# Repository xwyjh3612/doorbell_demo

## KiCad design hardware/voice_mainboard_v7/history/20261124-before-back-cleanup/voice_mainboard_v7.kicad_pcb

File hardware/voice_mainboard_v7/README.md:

# 语音对讲主板V7工作版

## 当前RGB版本

2026-11-24：单颗WS2812B-2020-V6（C52917434）已加入主板正面上沿，位置(72mm, 3mm)。GPIO39对应ESP模组32脚，经330Ω电阻驱动DI；100nF作局部去耦。厂家标明支持3.3V供电，新板的供电容差、启动、低压及光学效果仍需实测。

| 指示 | 含义 |
|---|---|
| 红色慢闪 | 未联网 / MQTT未就绪 |
| 绿色双闪 | 在线待机 |
| 蓝色快闪 | 呼叫、呼入、连接中 |
| 蓝色长亮带短熄灭 | 通话中 |

灯读取本地状态，由低优先级任务和RMT硬件驱动，不发送额外AT命令，不改变音频队列、主动丢旧包或官方协议。它不是独立供电指示灯或硬件看门狗。配置`CONFIG_VOICE_STATUS_INDICATOR_ENABLE`默认关闭；`tools/build-firmware.ps1 -Variant mainboard-v7`开启电源监测及RGB，开发板`voice-radar60`不包含这两项。两种固件的配置、编译包含/排除与链接符号已验证，灯色/闪烁/长运行时间的主机逻辑测试通过，未刷机或测试新主板。

本次按官方表核对全部已用GPIO，修复原版实际接到GPIO41的充电控制：GPIO38应接模组31脚，模组34脚实际为GPIO41。新RGB原理图、PCB、符号库与固件一致。旧版GPIO38暂停充电的说明不适用于未纠正的旧PCB。

当前ERC/DRC错误及警告、未连接、原理图连接差异均为0，实际填充GND为一个连通分量。只证明CAD连接，不是完整电气仿真或生产放行。当前证据以[rgb-validation.json](exports/rgb-validation.json)及[新版预览](exports/review.html)为准；加灯前的文件与检查在[历史快照](history/20261124-before-rgb/voice_mainboard_v7.kicad_pcb)。下文局部整理数据和费用均属于加灯前版本。

[公开价格](https://item.szlcsc.com/55827425.html)：少量0.5585元/颗、100颗0.3469元、1000颗0.3198元。加电阻、电容后按约0.4元/台材料预算；电阻、电容并未全部取得本次新报价，新增贴装/换料费用仍需审单。当前默认装配由116增加到119个元件。此前51.46/52.33元的条件预算需另加RGB材料和新增加工费，不能当成新版整单报价。

2026-11-24，用户授权由设计方决定技术路线。采用100×75mm、两层板，保留现有功能，按可靠性、成本和可制造性重新整理布局。

**加灯前完成的是局部供电布局优化与背面长地线清理，整板重新布局、器件定型和实物验证尚未完成，未生产放行。** V6原板保留；V7采用V6已通过几何检查的走线优化候选作为起点，不改变固件协议与主动丢旧包策略。

## 当前技术决定

| 项目 | 决定 | 状态 |
|---|---|---|
| 板层及尺寸 | 100×75mm两层，先保留现有接口和安装孔 | 已落实 |
| 主控 | 保留ESP32-S3-WROOM-1-N8R8，不为了减少几元改为需另外设计Flash/PSRAM的裸芯片方案 | 沿用；仍需采购报价及模组配置核对 |
| 4G | 按ML307C-DL贴装规划，第一阶段沿用AT通信；USB作为硬件备用，需重新布局与独立验证 | 主方案明确；新模组实测及USB验证未完成 |
| 音频 | 保留当前I2S功放及INMP441模块接口；先改善供电去耦和回流，不改已测试的音频协议 | 局部去耦已调整；音频整体分区待重排 |
| 电源 | 5V/2A外电，正常时直供系统；单节4.2V锂离子电池备用，经保护、升压和切换接管 | 架构明确；具体电芯、NTC、低电量峰值与热测试仍待确定 |
| 卡座 | 优先国产翻盖Nano SIM、保留检测功能；SMN-305-ARP7（C720512）为优先核查对象 | 公开1000件阶梯参考0.5977元。图纸下载返回403、未获得对应封装证据，因此暂未换入；现板仍保留JAE卡座 |
| 走线 | 水平/垂直优先、必要处45°；去掉绕路和无意义折返；电源、USB、射频按各自电气要求处理 | 部分落实；整板分区重排未完成 |
| 充电温度 | 目标电芯需明确允许充电温度；不沿用V6约−7℃的低温门限。优先设计带容差裕量的保守窗口 | 电芯与NTC准确规格确定后重算；现工作版阻值尚未更改 |
| 电量 | ESP ADC估算电量；保留外电接入和实际电源选择检测 | 现有硬件/代码接口保留；新板验收未完成 |

## 本次完成的局部修改

- 功放100nF C62与U14电源焊盘中心直线距离，从约5.63mm降到约1.95mm。
- 功放10µF C61与对应电源焊盘距离约4.21mm，较原位置缩短；它不是当前最佳完整布局，整板重排时还要继续改善。
- 充电输入C67与U16电源焊盘距离，从约8.05mm降到约2.62mm。
- 充电电池侧C68与U16 BAT焊盘距离，从约5.34mm降到约3.75mm。
- 重接局部电源与地，清理因电容移位遗留的无效支路。供电路径连通不代表动态、热与最大电流已经验证。
- 保留前一候选对主输入细线的修复。

上述数字是焊盘中心直线距离，不是环路长度、等效电感或实测噪声结果。[加灯前局部检查记录](history/20261124-before-rgb/exports/local-layout-validation.json)绑定当时PCB哈希；不使用旧版检查为新版背书。

## 后续工程工作

按电源局部环路→主控/音频分区→4G/SIM/天线区→USB接口与差分线路→整板规则、制造BOM和成本的顺序推进。所有局部修改都重新运行原生DRC和原理图连接一致性检查。

生产前仍须完成准确料号/封装、NTC温度窗口、实际电芯、低电量启动与接管、峰值电流及温升、USB/RF资格、刷机与长通话验证。软件模型和ERC/DRC均不代替新主板实测。

## 背面整理结果与量产核算

2026-11-24新增：保留焊盘位置、原理图连接、电池隔离负极及局部电源回流，简化可安全缩短的连续走线；清理与铺铜重复的长地线。两处失去接地的焊盘（C10、Q7）补接背面地铜，新增两个地过孔，保留原有地过孔。

| 背面指标 | 整理前 | 整理后 |
|---|---:|---:|
| 线段数 | 1109 | 571 |
| 非共线二路连接点（连续转角） | 632 | 309 |
| 地线线段数 | 664 | 148 |

上述数字统计铜线对象；移除冗余地线后由实际铺铜承担连接，不能将铜线长度下降解读为回流路径缩短或电阻降低。原生DRC错误/警告/未连接/原理图连接差异均为0，包含孔洞的填充地铜、焊盘、线与通孔连通审查为一个GND分量。该审查只证明连接，未验证电源动态、温升或EMC。

整理前PCB及其哈希记录保存在[历史快照](history/20261124-before-back-cleanup/voice_mainboard_v7.kicad_pcb)。加灯前结果见[背面前后对比](history/20261124-before-rgb/exports/review.html)与[当时审查记录](history/20261124-before-rgb/exports/back-cleanup-validation.json)。走线视图暂隐藏铺铜，实际生产工作文件保留铺铜。

1000块的降本核算：按用户4G 10元、ESP32-S3 N8R8 12元目标价，其余有公开/历史候选参考的优先重算，功放采用4.52元公开参考价。国产SIM C720512图纸、封装及检测触点尚待核，未写入PCB。全接口候选方案约52.33元/块；仅雷达与TTL排针不默认安装、保留焊孔的可选量产方案约51.46元/块。后者插件节省按历史0.09元/焊点推算，本次网站防护页面阻止取得新公开计算结果，仍非嘉立创完整审单报价。按已保存公开4G/ESP参考价替代用户目标，可选量产方案将增加15.01元/块。

成本与装配选项尚未改变当前样机的默认BOM；加灯前样机保留116个装配元件，当前RGB工作版为119个。详见[逐项成本与采购边界](cost/量产降本核算.md)。本次不因走线整理计入PCB单价节省。

## 充电与无电池使用状态

2026-11-24核查：当前未实现80%停充/70%再充；现有电源监测仅在呼叫、通话、OTA暂停充电，功能默认关闭。TP4056-MS按约4.2V、名义300mA充电。已有GPIO38→Q7→CE可供后续实现电量迟滞控制，无需另加控制芯片。

外电通路独立于电池，设计上支持不装电池、仅插5V电源。电池及NTC均不接时，现温度分压约0.89×VCC，按芯片规格暂停充电；整板外电启动与负载能力仍待实板测试。ADC读到电压不能单独证明已安装电池，固件不得将无电芯的输出电容电压当作有效SOC。

本次已运行当前阻值的ngspice被动/理想控制子电路，并核对实际PCB引脚网络；未进行电芯化学充放电、充电IC/升降压完整厂家模型或整板电气仿真。现假设10k/B3950 NTC的名义温度窗口约−7～38.5℃，−5℃仍允许充电，必须按选定电芯修正。TEMP短到地会禁用温度监测，不能视为自动停充。详见[充放电与无电池核查记录](exports/charge-supply-audit/充放电核查.md)。

[PCB工作文件](voice_mainboard_v7.kicad_pcb) · [原理图](voice_mainboard_v7.kicad_sch) · [当前检查记录](exports/rgb-validation.json)

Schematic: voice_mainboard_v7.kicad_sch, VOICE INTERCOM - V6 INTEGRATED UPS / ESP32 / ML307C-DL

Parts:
C4, C6, C7, C59, C60: 22u 16V; C_0805_2012Metric
C5: 22u 16V; C_0805_2012Metric; not fitted
C8: OCV471M1ATR-1010 470u 10V; CP_Elec_10x10.5
C10: 10u 10V; C_0805_2012Metric
C11, C13, C14, C15, C16, C17, C18, C58, C62, C69, C70: 100n; C_0603_1608Metric
C12: 33p; C_0603_1608Metric
C19, C29: CL10B103KB8NNNC; C_0603_1608Metric
C20, C28: CL10B104KB8NNNC C1591; C_0603_1608Metric
C24, C25: RF MATCH SHUNT DNP; C_0603_1608Metric; not fitted
C26: 100n MIC; C_0603_1608Metric
C37: 22p MODEM CFF; C_0603_1608Metric
C56: 1u EN delay; C_0603_1608Metric
C57: 22u; C_0805_2012Metric
C61: 10u; C_0805_2012Metric
C63: 22p ESP CFF; C_0603_1608Metric
C64, C65, C66, C71, C72, C73: 22u 10V X5R; C_0805_2012Metric
C67, C68: 10u 10V X5R; C_0805_2012Metric
D1: SRV05-4 MSKSEMI; SOT-23-6
F1: ASMD1812-400-16V C55014590; Fuse_1812_4532Metric
J1: HX DC005-2.5-T 3A C18357600; HX_DC005_2p5_T
J8: MODEM DOWNLOAD STRAP OPEN NORMAL; PinHeader_1x02_P2.54mm_Vertical; not fitted
J10: JAE SF72S006 SIM CANDIDATE; JAE_SIM_Card_SF72S006
J11: LTE ANT U.FL; U.FL_Hirose_U.FL-R-SMT-1_Vertical
J12: MODEM USB SERVICE VBUS DM DP GND; PinHeader_1x04_P2.54mm_Vertical; not fitted
J14: INMP441 MODULE 3V3 GND BCLK WS SD; PinHeader_1x05_P2.54mm_Vertical
J15: SPEAKER BTL + / - NEVER GND; PinHeader_1x02_P2.54mm_Vertical
J16: OPTIONAL RADAR 5V GND RX6 TX8; PinHeader_1x04_P2.54mm_Vertical
J17: EXTERNAL CALL BUTTON; PinHeader_1x02_P2.54mm_Vertical
J18: TTL GND TX43 RX44 5V; PinHeader_1x04_P2.54mm_Vertical
J22: USB HOST RESERVE GND DP20 DM19; PinHeader_1x03_P2.54mm_Vertical; not fitted
J23: 1S CELL + / - / NTC; PinHeader_1x03_P2.54mm_Vertical
L1: SWPA6045S2R2MT C83455; L_Sunlord_SWPA6045S
L4: SWPA6045S2R2MT; L_Sunlord_SWPA6045S
L5: 2.2uH SWPA4030S 3A TARGET; L_Sunlord_SWPA4030S
Q1, Q2, Q4, Q5: 2N7002K-7 C85047; SOT-23
Q3: BSS84,215 C493579; SOT-23
Q6: DMP2035U-7 C110499; SOT-23
Q7: 2N7002K-7; SOT-23
R2: 100k 0.1% MODEM RH; R_0603_1608Metric
R3: 18.7k 0.1% MODEM RL; R_0603_1608Metric
R4, R12, R21, R68, R72, R73, R74: 10k; R_0603_1608Metric
R5, R6, R8, R15, R16, R32, R69: 100k; R_0603_1608Metric
R7: 4.7k AUTO ON DNP; R_0603_1608Metric; not fitted
R9, R10, R11: 22R; R_0603_1608Metric
R13: 0R RF SERIES; R_0603_1608Metric
R14: 10k BOOT; R_0603_1608Metric
R17: 150k 1%; R_0603_1608Metric
R18, R20: 100k 1%; R_0603_1608Metric
R19: 10k 1%; R_0603_1608Metric
R26: 0R USB SERVICE DP; R_0402_1005Metric
R27: 0R USB SERVICE DM; R_0402_1005Metric
R28: 0R USB HOST DP; R_0402_1005Metric; not fitted
R29: 0R USB HOST DM; R_0402_1005Metric; not fitted
R30: 0R VBUS FROM SERVICE; R_0603_1608Metric
R31: 0R VBUS DETECT FROM SYSTEM DNP; R_0603_1608Metric; not fitted
R57: 10k EN; R_0603_1608Metric
R58: 0R RADAR POWER OPTIONAL; R_0603_1608Metric; not fitted
R59: 100k 1% RH ESP; R_0603_1608Metric
R60: 22.1k 1% RL ESP; R_0603_1608Metric
R61: 73.2k 0.1%; R_0603_1608Metric
R62: 10k 0.1%; R_0603_1608Metric
R63: 30k 1% ISET; R_0603_1608Metric
R64: 4k 1% 300mA; R_0603_1608Metric
R65: 6.19k 1% NTC TOP; R_0603_1608Metric
R66: 49.9k 1% NTC BOTTOM; R_0603_1608Metric
R67: 0R NTC LINK; R_0603_1608Metric
R70: 100k 0.1% PR TOP; R_0603_1608Metric
R71: 33.2k 0.1% PR BOTTOM; R_0603_1608Metric
R75: 0R LEFT CHANNEL; R_0603_1608Metric
R76: 0R 12dB; R_0603_1608Metric
SW1, SW2, SW3: TACT 4.5x4.5 SMD; SW_SPST_TL3342
TP1: POWER_BUS; V6_BOARD_TP1
TP2: MODEM_STATE_1V8; V6_BOARD_TP2
TP3: MODEM_NETLIGHT; V6_BOARD_TP3
TP4: DEBUG_ESP_TX43; V6_BOARD_TP4
TP5: DEBUG_ESP_RX44; V6_BOARD_TP5
TP6: GND; V6_BOARD_TP6
TP7: VIN_PROTECTED; V6_BOARD_TP7
TP8: POWER_BUS; V6_BOARD_TP8
TP9: SYS_5V UPS OUTPUT TEST; V6_BOARD_TP9
TP10: ESP_3V3; V6_BOARD_TP10
TP12: MUX ST / GPIO47; V6_BOARD_TP12
TP13: BAT BOOST 5V; V6_BOARD_TP13
TP14: CELL NEG isolated; V6_BOARD_TP14
TP15: DBG_TX_1V8; V6_BOARD_TP15
TP16: DBG_RX_1V8; V6_BOARD_TP16
TP17: MODEM_1V8; V6_BOARD_TP17
U1: ML307C-DL; ML307C_DL_109_LIBRARY_REVIEW
U2, U13: SY8089A1AAC; SOT-23-5
U3, U4, U5: SN74LVC1T45DBVR; SOT-23-6
U7: ESP32-S3-WROOM-1-N8R8; V6_U7_SMD_LAND_MATCH
U14: MAX98357AETE+; V6_U14_SMD_LAND_MATCH
U15: ETA1096E8A; ETA1096_ESOP8
U16: TP4056-MS; SOIC-8-1EP_3.9x4.9mm_P1.27mm_EP2.29x3mm
U17: XB7608AJL; XB7608_CPC5
U18: TPS2117DRLR; TI_DRL0008A
U19: ME2807A30M3G; SOT-23

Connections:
AMP_GAIN: R76.1, U14.2
AMP_SD: R75.2, U14.4
BAT_ADC2: C28.1, R17.2, R18.1, U7.38
BAT_ADC_EN9: Q4.1 (G), R16.1, U7.17
BAT_BOOST_5V: C65.1, C66.1, C73.1, R61.1, TP13.1, U15.7 (OUT), U18.6 (VIN2)
BAT_DIV_SW: Q3.3 (D), R17.1
BAT_GATE: Q3.1 (G), Q4.3 (D), R15.2
BAT_SENSE_IN: C64.1, C68.1, C69.1, C70.1, J23.1, L4.1, Q3.2 (S), R15.1, U15.4 (IN), U16.5 (BAT), U17.1 (VDD), U19.3 (VIN)
BAT_TEMP: R65.2, R66.1, R67.2, U16.1 (TEMP)
BOOST_EN: U15.2 (EN), U19.1 (RESET_N)
BUCK_FB: C37.2, R2.2, R3.1, U2.5 (FB)
BUCK_SW: L1.1, U2.3 (LX)
CALL_BOOT0: J17.1, R14.2, SW1.1, U7.27
CELL_NEG: C69.2, J23.2, TP14.1, U17.2 (CELL_GND), U17.3 (CELL_GND)
CELL_NTC: J23.3, R67.1
CHG_ACTIVE_N: R73.2, U7.25 (IO48), U16.7 (CHRG)
CHG_CE: Q7.3 (D), R68.2, U16.8 (CE)
CHG_DISABLE_IO38: Q7.1 (G), R69.1, U7.34 (IO38)
CHG_FULL_N: R74.2, U7.39 (IO1), U16.6 (STDBY)
CHG_PROG: R64.1, U16.2 (PROG)
DBG_RX_1V8: TP16.1, U1.38 (DBG_RXD)
DBG_TX_1V8: TP15.1, U1.39 (DBG_TXD)
DEBUG_ESP_RX44: J18.3, TP5.1, U7.36
DEBUG_ESP_TX43: J18.2, TP4.1, U7.37
ESP_3V3: C13.1, C15.1, C17.1, C26.1, C57.1, C58.1, C60.1, C63.1, J14.1, L5.2, R4.1, R14.1, R21.1, R57.1, R59.1, R72.1, R73.1, R74.1, TP10.1, U3.1 (VCCA), U3.5 (DIR), U4.1 (VCCA), U5.1 (VCCA), U5.5 (DIR), U7.2 (3V3)
ESP_DTR4: R5.1, U5.3 (A), U7.4
ESP_EN: C56.1, R57.2, SW2.1, U7.3 (EN)
ESP_FB: C63.2, R59.2, R60.1, U13.5 (FB)
ESP_RX18: U4.3 (A), U7.11
ESP_SW: L5.1, U13.3 (SW)
ESP_TX17: R4.2, U3.3 (A), U7.10
ESP_USB_DM19: J22.3, R29.2, U7.13
ESP_USB_DP20: J22.2, R28.2, U7.14
EXT_DETECT_GATE: C29.1, Q5.1 (G), R19.2, R20.1
EXT_PRESENT_N_IO10: Q5.3 (D), R21.2, U7.18
GND: C4.2, C5.2, C6.2, C7.2, C8.2, C10.2, C11.2, C12.2, C13.2, C14.2, C15.2, C16.2, C17.2, C18.2, C19.2, C20.2, C24.2, C25.2, C26.2, C28.2, C29.2, C56.2, C57.2, C58.2, C59.2, C60.2, C61.2, C62.2, C64.2, C65.2, C66.2, C67.2, C68.2, C70.2, C71.2, C72.2, C73.2, D1.2 (GND), J1.2 (SLEEVE_MFR2), J8.2, J10.C5 (GND), J10.CSW (DETECT_COM), J10.SH (SHIELD), J11.2, J12.4, J14.2, J16.2, J17.2, J18.1, J22.1, Q1.2 (S), Q2.2 (S), Q4.2 (S), Q5.2 (S), Q7.2 (S), R3.2, R5.2, R6.2, R7.2, R8.2, R16.2, R18.2, R20.2, R32.2, R60.2, R62.2, R63.2, R64.2, R66.2, R69.2, R71.2, R76.2, SW1.2, SW2.2, SW3.2, TP6.1, U1.1 (GND), U1.10 (GND), U1.27 (GND), U1.34 (GND), U1.36 (GND), U1.37 (GND), U1.40 (GND), U1.41 (GND), U1.45 (GND), U1.46 (GND), U1.47 (GND), U1.48 (GND), U1.70 (GND), U1.71 (GND), U1.72 (GND), U1.73 (GND), U1.88 (GND), U1.89 (GND), U1.90 (GND), U1.91 (GND), U1.92 (GND), U1.93 (GND), U1.94 (GND), U1.95 (GND), U2.2 (GND), U3.2 (GND), U4.2 (GND), U4.5 (DIR), U5.2 (GND), U7.1 (GND), U7.40 (GND), U7.41 (GND), U13.2 (GND), U14.3, U14.11, U14.15, U14.17, U15.1 (GP), U15.8 (GP), U15.9 (AGND_EP), U16.3 (GND), U16.9 (EP), U17.4 (PACK_NEG), U17.5 (PACK_NEG), U18.1 (GND), U19.2 (GND)
I2S_MIC_BCLK14: J14.3, U7.22
I2S_MIC_DATA12: J14.5, U7.20
I2S_MIC_WS13: J14.4, U7.21
I2S_SPK_BCLK15: U7.8, U14.16
I2S_SPK_DATA7: U7.7, U14.1
I2S_SPK_WS16: U7.9, U14.14
MODEM_1V8: C14.1, C16.1, C18.1, R12.1, TP17.1, U1.24 (VDD_EXT), U3.6 (VCCB), U4.6 (VCCB), U5.6 (VCCB)
MODEM_3V8: C6.1, C7.1, C10.1, C11.1, C12.1, C37.1, L1.2, R2.1, TP1.1, TP8.1, U1.42 (VBAT), U1.43 (VBAT)
MODEM_BOOT_N: J8.1, U1.82 (BOOT_MODE)
MODEM_NETLIGHT: TP3.1, U1.16 (NETLIGHT)
MODEM_PWRKEY_N: Q1.3 (D), R7.1, SW3.1, U1.7 (PWR_ON/OFF)
MODEM_RESET_N: C19.1, Q2.3 (D), U1.15 (RESET)
MODEM_STATE_1V8: TP2.1, U1.25 (STATE)
M_DTR_1V8: U1.19 (UART0_DTR), U5.4 (B)
M_RX_1V8: U1.17 (UART0_RXD), U3.4 (B)
M_SIM_CLK: R10.1, U1.13 (USIM0_CLK)
M_SIM_DATA: R9.1, U1.11 (USIM0_DATA)
M_SIM_RESET: R11.1, U1.12 (USIM0_RESET)
M_TX_1V8: U1.18 (UART0_TXD), U4.4 (B)
M_USB_DM: R27.1, R29.1, U1.60 (USB_DM)
M_USB_DP: R26.1, R28.1, U1.59 (USB_DP)
PWRKEY_CTL: Q1.1 (G), R6.1, U7.19
RADAR_5V: J16.1, R58.2
RADAR_RX6: J16.3, U7.6
RADAR_TX8: J16.4, U7.12
RESET_CTL: Q2.1 (G), R8.1, U7.23
REVERSE_GATE: Q6.1 (G), R32.1
RF_ANT: C24.1, R13.1, U1.35 (ANT_MAIN)
RF_FEED: C25.1, J11.1, R13.2
SERVICE_USB_DM: J12.2, R27.2
SERVICE_USB_DP: J12.3, R26.2
SERVICE_USB_VBUS: J12.1, R30.1
SIM_CLK: D1.3 (IO), J10.C3 (CLK), R10.2
SIM_DATA: D1.1 (IO), J10.C7 (IO), R9.2
SIM_DETECT: J10.DSW (DETECT), R12.2, U1.79 (USIM0_DET)
SIM_RESET: D1.4 (IO), J10.C2 (RST), R11.2
SIM_VCC: C20.1, D1.5 (VCC), D1.6 (IO), J10.C1 (VCC), U1.14 (USIM0_PWR)
SPK_MINUS: J15.2, U14.10
SPK_PLUS: J15.1, U14.9
SUPPLY_BAT_N47: R72.2, TP12.1, U7.24 (IO47), U18.8 (ST)
SYS_5V: C4.1, C5.1, C8.1, C59.1, C61.1, C62.1, C72.1, R31.1, R58.1, R75.1, TP9.1, U2.1 (EN), U2.4 (IN), U13.1 (EN), U13.4 (VIN), U14.7, U14.8, U18.2 (VOUT), U18.7 (VOUT_COMMON)
UPS_FB: R61.2, R62.1, U15.5 (FB)
UPS_ISET: R63.1, U15.6 (ISET)
UPS_PR1: R70.2, R71.1, U18.4 (PR1)
UPS_SW: L4.2, U15.3 (SW)
USB_DETECT_5V: R30.2, R31.2, U1.61 (USB_VBUS)
VIN_DC: F1.1, J1.4 (CENTER_PLUS_MFR4), J18.4, R19.1
VIN_FUSED: F1.2, Q6.3 (D)
VIN_PROTECTED: C67.1, C71.1, Q6.2 (S), R65.1, R68.1, R70.1, TP7.1, U16.4 (VCC), U18.3 (VIN1), U18.5 (MODE)

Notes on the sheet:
01 INPUT / MODEM 3.80856V
02 ETA1096 / CHARGE / PROTECT / MUX
03 ML307 / UART / RESET
04 SIM / RF / USB RESERVE
05 ESP / BOOT / ADC / TTL
06 ESP3.315V / I2S AUDIO
07 TEST PADS
V6: V6 UPS: ETA1096 battery boost + TPS2117 external priority; two SY8089A1 bucks; nominal5V audio/radar.
Battery J23 = CELL+ / isolated CELL- / NTC. CELL- must NOT short to systemGND; U17 is protection.
J18 TTL = GND / ESP TX43 / ESP RX44 / adapter5V. Do not parallel TTL5V and main adapter.
SIM JAE footprint retained until exact cheap socket drawing; GPIO6/8 radar; GPIO47 muxST; ADC2 with GPIO9 gate; GPIO38 charge pause; GPIO48/1 charge status.
Electrical/geometry checks do not validate load, startup, temperature, RF, USB or call function.

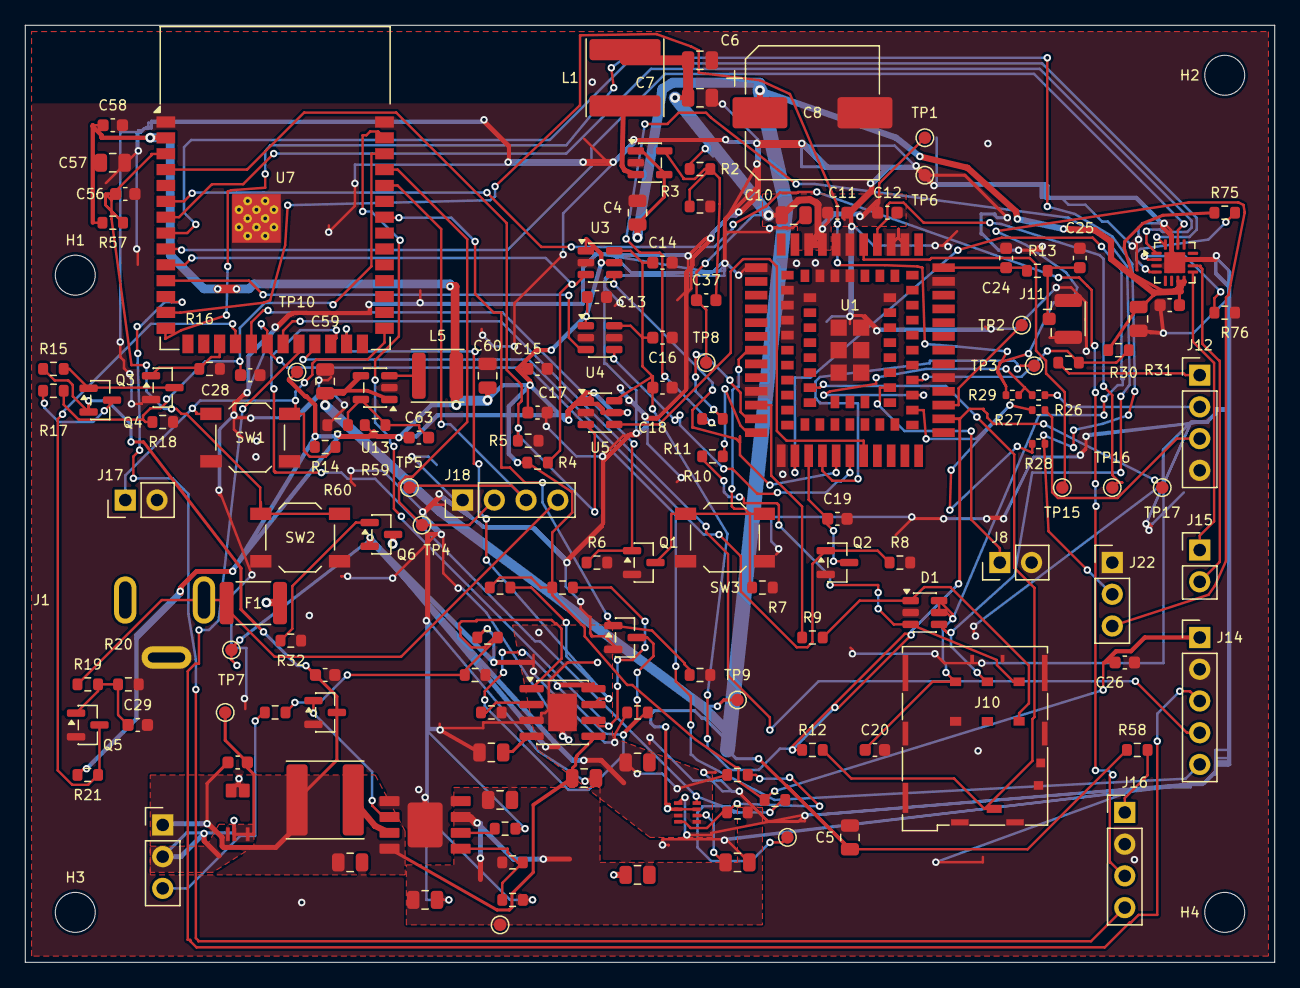
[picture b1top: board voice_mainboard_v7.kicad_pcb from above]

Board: 2 copper layers, 100.0 x 75.0 mm, 147 parts (0 on the bottom side), 85 nets.

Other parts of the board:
H1: M3; V6_BOARD_H1
H2: M3; V6_BOARD_H2
H3: M3; V6_BOARD_H3
H4: M3; V6_BOARD_H4
